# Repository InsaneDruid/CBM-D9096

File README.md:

# CBM D9096 - a PetSD+ variant
Inspired by the work of Steve J. Gray and his cbmSD-mini, the CBM D9096 is a cost- and feature-reduced version of Nils Eiler's PetSD+ board, designed specifically for headless operation in an external enclosure, connected with a true GPIB cable, similar to a D9060 or D9090.

[Schematic](https://github.com/InsaneDruid/cbm-d9096/blob/main/cbm-d9096/cbm-d9096.pdf "Schematic")  

[Bill of Materials](https://htmlpreview.github.io/?https://github.com/InsaneDruid/cbm-d9096/blob/main/cbm-d9096/bom/cbm-d9096_bom.html "Bill of Materials")

## The features
A 24-pin Centronics IEEE488/GBIP connector allows the CBM D9096 to be placed anywhere in the IEEE488 chain. This also eliminates the need for a second connector, as the IEEE488 connectors are designed to be stackable.
The SD-Card interface, the status LED and the RESET Button are implemented as pinheaders, so that the main PCB with the GBIB plug and power port can be spaced away from the parts the user needs to interact with, giving flexibility in the design of a case. Additionally, the option to use a Molex Mini Fit Jr Power Plug for connecting to an internal power supply has been implemented.

## The features that got removed
The display with its display controller, the clock, the clock battery, the buttons for interfacing with the display, and the IEC connector have been removed. The circuitry to support SD cards (mainly the 3.3 V power regulator) has also been moved to the readily available card modules. This allows the use of SD and MicroSD modules and the aforementioned flexibility in positioning these modules in a housing.

## The SD card adapters - 1.1.0 adding more options
The board now features two headers to attach readily available SD card and Micro SD card modules.
The one marked *5V SPI SD-CARD* (J3) is operating at 5 volts! The card modules attached here  MUST have appropriate level shifters installed.
Tis applies to nearly all readily available Micro SD card modules, but only some older SD card modules.
Tested and working boards are: *DEBO MICROSD 2* and *C-Control Pro Nr. 197220*
Boards that just use a voltage regulator and some passive resistors do NOT work on this header!

To use the 5V SPI SD-CARD header, JP1 needs to be set to position 2-3 (leftwards)

The one marked *3.3V SPI SD-CARD* (J5) is operating at 3.3 volts using a TXU0304 SPI level shifter and a 3.3V regulator.The card modules attached here don't need (and should *not* have!) their own level shifters.
This applies to nearly all readily available full size SD card modules. Note: this port supplies 3.3V OR 5V to the card module. Select the appropriate pin depending on the card module to connect. 

To use the 3.3V SPI SD-CARD header, JP1 needs to be set to position 1-2 (rightwards)

*Attention!* you CANNOT use two SD card modules at the same time!

## The *card detect* and *write protect* signals
Both SD card headers J3 & J5 have ground pin headers available behind the pins for the card detect ("CD") and write protect ("WP) signals (marked J4 & J6). If the attached card module doesn't provide these signals, for example all Micro SD modules, connect a 2.54mm jumper between the CD and or WP pins of J3/J5 and the associated pin of J4/J6 to permanently tie these signals to ground (permanently enable them).

## The Firmware
Andy Grady has provided a customized [firmware](https://github.com/InsaneDruid/cbm-d9096/blob/main/firmware/cbm-d9096.bin "cbm-d9096.bin") in which the button input is completely deactivated, so that the use of a voltage divider and filtered analog voltage is no longer necessary and with V1.1.0 these supporting parts are omitted. 

### Firmware installation
* Flash the [bootloader](https://github.com/InsaneDruid/cbm-d9096/blob/main/firmware/new-bootloader-for-16-MHz-petSD-plus.hex "new-bootloader-for-16-MHz-petSD-plus.hex") file to the Atmega. 
    * Set the fuse bits to Low: F7, High: D2, Extended: FC
        * low: CKSEL3=low
        * high: SPIEN=0, EESAVE=0, BOOTSZ1=0, BOOTRST=0
        * extended: BODLEVEL1=0, BODLEVEL0=0
* Install the Atmega in the board.
* Copy the [firmware](https://github.com/InsaneDruid/cbm-d9096/blob/main/firmware/cbm-d9096.bin "cbm-d9096.bin") to a FAT16 or FAT32 formatted SD-card.
* Insert the prepared card and turn on the d9096.
* On startup, the bootloader will program the firmware to the Atmega.
    * The file name is not important - the bootloader checks for a hardware tag and version number in the file.
    * During the flash operation the busy LED flickers rapidly.
    * If a valid firmware is not found, the boot loader will flash the error LED for two seconds and try to find a valid file once more.

## The LED options
The board is designed to be configured for a 2 LED or 3 LED setup:

### 2 LED variant
In the 2 LED variant power and error are combined in a *bidirectional* dual-color led (NOT common cathode or common anode!), reminiscent of how the CBM drives did. Activity is shown on a standard LED.

* install a jumper wire in place of R2
* connect a bidirectional LED between pins 3 (error) and 4 (power) of J2
* connect a standard LED between pins 1(activity) and 2 (gnd) of J2

### 3 LED variant
In the 3 LED variant power and error as well as activity are displayed with independent LED.

* don't install R4 (leave open)
* install a 330 Ohm resistor in R1, R2, R3
* connect power LED between pins 4 (power) and 2 (GND) of J2
* connect error LED between pins 3 (error) and 2 (GND) of J2
* connect activity LED between pins 1 (activity) and 2 (GND) of J2

## The printable housing option
To adapt the cheaply available Bahar enclosue 150*140*70mm project box, 3d printable parts are available.

[Printable parts on printables.com](https://www.printables.com/model/878141-cbm-d9069/ "Printable parts on printables.com")  

## The License
This work is licensed under a Creative Commons Attribution-ShareAlike 4.0 International License.  
See https://creativecommons.org/licenses/by-sa/4.0/.

## The Credits
This work would not have been possible without the work of Nils Eilers and his wonderful PetSD+. In addition, Steve J. Gray had the idea of a similar cost- and feature-reduced version of the PetSD+ when he designed his cbmSD-mini, which uses board-edge connectors and is designed to connect directly to the PETs board and case. This work inspired the CBM D9096.

Special thanks also go to Andy Grady for the customized firmware.

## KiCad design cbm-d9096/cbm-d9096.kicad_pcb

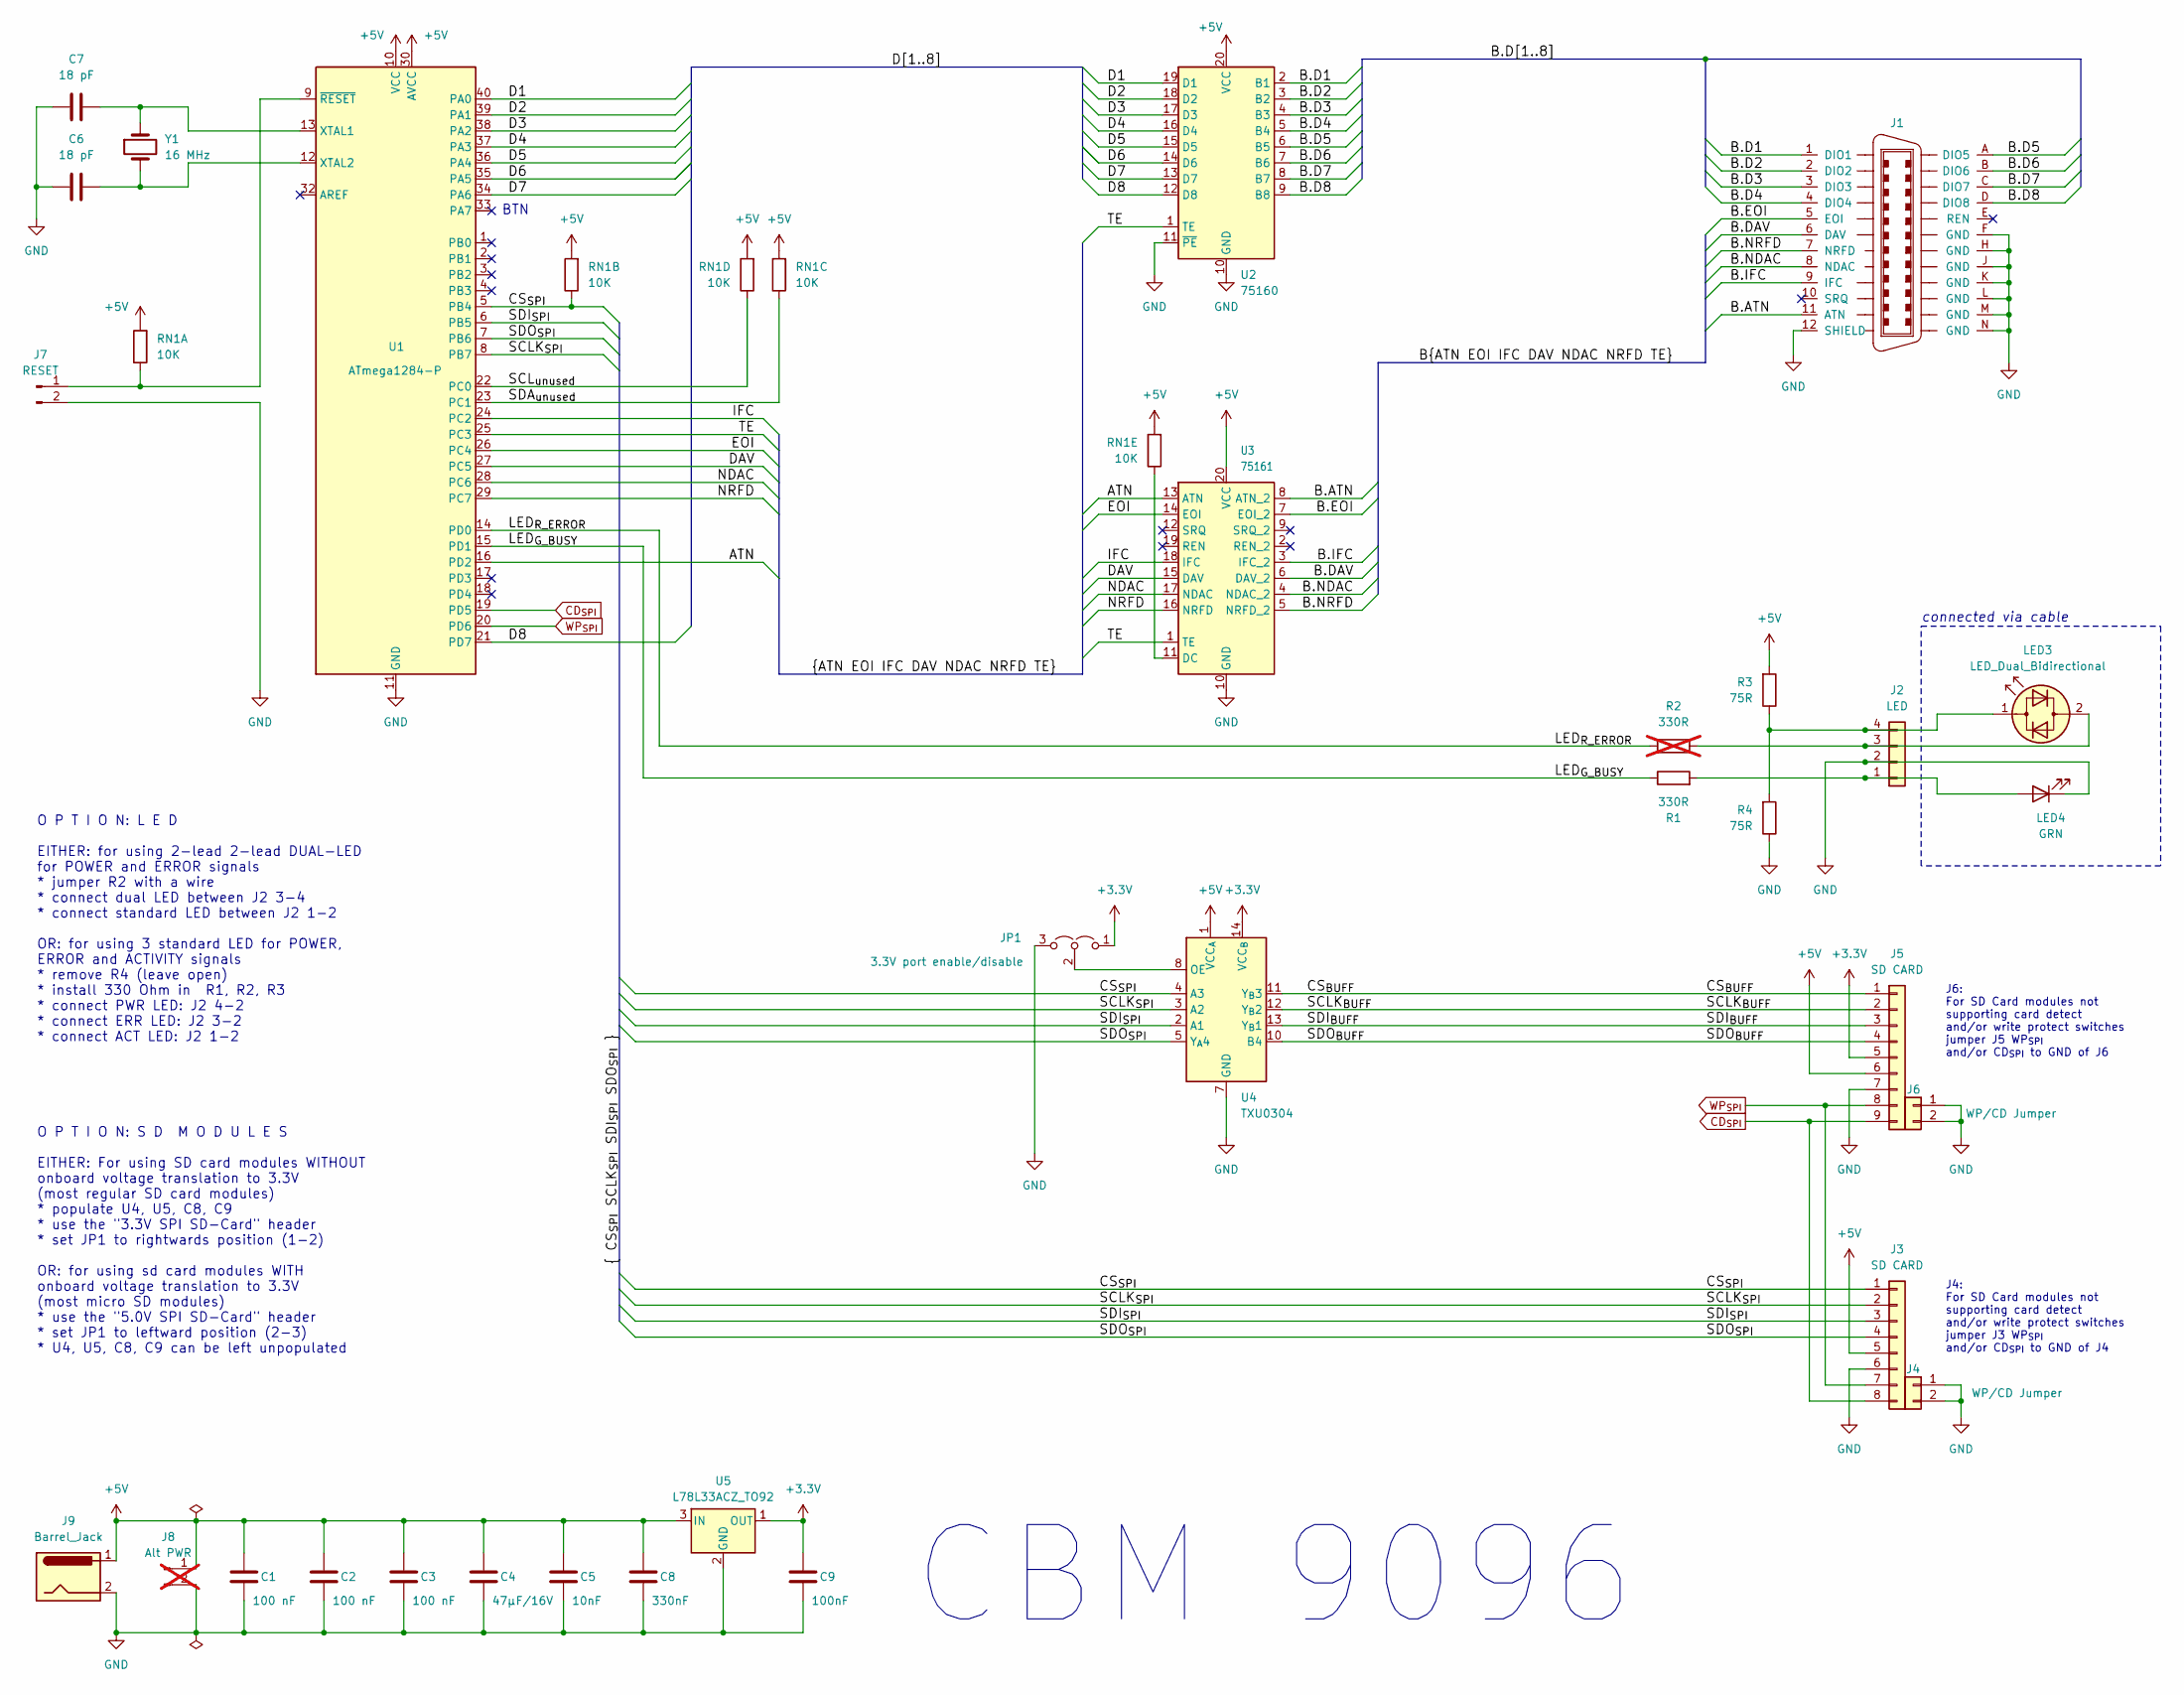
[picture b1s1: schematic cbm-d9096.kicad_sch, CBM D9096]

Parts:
C1, C2, C3: 100 nF; C_Disc_D3.8mm_W2.6mm_P2.50mm
C4: 47µF/16V; CP_Radial_D6.3mm_P2.50mm
C5: 10nF; C_Disc_D3.8mm_W2.6mm_P2.50mm
C6, C7: 18 pF; C_Disc_D3.8mm_W2.6mm_P2.50mm
C8: 330nF; C_Disc_D3.8mm_W2.6mm_P2.50mm
C9: 100nF; C_Disc_D3.8mm_W2.6mm_P2.50mm
J1: IEEE488 Header; centronix-24-female
J2: LED; PinHeader_1x04_P2.54mm_Vertical
J3: SD CARD; PinHeader_1x08_P2.54mm_Vertical
J4, J6: WP/CD Jumper; PinHeader_1x02_P2.54mm_Vertical
J5: SD CARD; PinHeader_1x09_P2.54mm_Vertical
J7: RESET; PinHeader_1x02_P2.54mm_Vertical
J8: Alt PWR; Molex_Mini-Fit_Jr_5566-02A_2x01_P4.20mm_Vertical; not fitted
J9: Barrel_Jack; BarrelJack_Horizontal
JP1: 3.3V port enable/disable; PinHeader_1x03_P2.00mm_Vertical
LED3: LED_Dual_Bidirectional
LED4: GRN; LED_D3.0mm_Clear
R1: 330R; R_Axial_DIN0207_L6.3mm_D2.5mm_P10.16mm_Horizontal
R2: 330R; R_Axial_DIN0207_L6.3mm_D2.5mm_P10.16mm_Horizontal; not fitted
R3, R4: 75R; R_Axial_DIN0207_L6.3mm_D2.5mm_P10.16mm_Horizontal
RN1: 10K; R_Array_SIP6
U1: ATmega1284-P; DIP-40_W15.24mm_Socket
U2: 75160; DIP-20_W7.62mm_Socket
U3: 75161; DIP-20_W7.62mm_Socket
U4: TXU0304; TSSOP-14_4.4x5mm_P0.65mm
U5: L78L33ACZ_TO92; TO-92L_Inline_Wide
Y1: 16 MHz; Crystal_HC49-4H_Vertical

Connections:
+3.3V: C9.1, J5.5, JP1.1 (A), U4.14 (VCC_{B}), U5.1 (OUT)
+5V: C1.2, C2.2, C3.2, C4.1, C5.1, C8.1, J3.5, J5.6, J8.1, J9.1, R3.2, RN1.1 (R1), U1.10 (VCC), U1.30 (AVCC), U2.20 (VCC), U3.20 (VCC), U4.1 (VCC_{A}), U5.3 (IN)
/ATN: U1.16 (PD2), U3.13 (ATN)
/B.ATN: J1.11 (ATN), U3.8 (ATN_2)
/B.D1: J1.1 (DIO1), U2.2 (B1)
/B.D2: J1.2 (DIO2), U2.3 (B2)
/B.D3: J1.3 (DIO3), U2.4 (B3)
/B.D4: J1.4 (DIO4), U2.5 (B4)
/B.D5: J1.A (DIO5), U2.6 (B5)
/B.D6: J1.B (DIO6), U2.7 (B6)
/B.D7: J1.C (DIO7), U2.8 (B7)
/B.D8: J1.D (DIO8), U2.9 (B8)
/B.DAV: J1.6 (DAV), U3.6 (DAV_2)
/B.EOI: J1.5 (EOI), U3.7 (EOI_2)
/B.IFC: J1.9 (IFC), U3.3 (IFC_2)
/B.NDAC: J1.8 (NDAC), U3.4 (NDAC_2)
/B.NRFD: J1.7 (NRFD), U3.5 (NRFD_2)
/CS_{BUFF}: J5.1, U4.11 (Y_{B}3)
/CS_{SPI}: J3.1, RN1.3 (R2.2), U1.5 (PB4), U4.4 (A3)
/D1: U1.40 (PA0), U2.19 (D1)
/D2: U1.39 (PA1), U2.18 (D2)
/D3: U1.38 (PA2), U2.17 (D3)
/D4: U1.37 (PA3), U2.16 (D4)
/D5: U1.36 (PA4), U2.15 (D5)
/D6: U1.35 (PA5), U2.14 (D6)
/D7: U1.34 (PA6), U2.13 (D7)
/D8: U1.21 (PD7), U2.12 (D8)
/DAV: U1.27 (PC5), U3.15 (DAV)
/EOI: U1.26 (PC4), U3.14 (EOI)
/IFC: U1.24 (PC2), U3.18 (IFC)
/LED_{G_BUSY}: R1.1, U1.15 (PD1)
/LED_{R_ERROR}: R2.1, U1.14 (PD0)
/NDAC: U1.28 (PC6), U3.17 (NDAC)
/NRFD: U1.29 (PC7), U3.16 (NRFD)
/SCLK_{BUFF}: J5.2, U4.12 (Y_{B}2)
/SCLK_{SPI}: J3.2, U1.8 (PB7), U4.3 (A2)
/SCL_{unused}: RN1.5 (R4.2), U1.22 (PC0)
/SDA_{unused}: RN1.4 (R3.2), U1.23 (PC1)
/SDI_{BUFF}: J5.3, U4.13 (Y_{B}1)
/SDI_{SPI}: J3.3, U1.6 (PB5), U4.2 (A1)
/SDO_{BUFF}: J5.4, U4.10 (B4)
/SDO_{SPI}: J3.4, U1.7 (PB6), U4.5 (Y_{A}4)
/TE: U1.25 (PC3), U2.1 (TE), U3.1 (TE)
CD_{SPI}: J3.8, J5.9, U1.19 (PD5)
GND: C1.1, C2.1, C3.1, C4.2, C5.2, C6.1, C7.1, C8.2, C9.2, J1.12 (SHIELD), J1.F (GND), J1.H (GND), J1.J (GND), J1.K (GND), J1.L (GND), J1.M (GND), J1.N (GND), J2.2, J3.6, J4.1, J4.2, J5.7, J6.1, J6.2, J7.2, J8.2, J9.2, JP1.3 (B), LED4.1 (K), R4.1, U1.11 (GND), U1.31 (GND), U2.10 (GND), U2.11 (~PE), U3.10 (GND), U4.7 (GND), U5.2 (GND); also elsewhere on the board
unnamed: J2.1, LED4.2 (A), R1.2
unnamed: J2.3, LED3.2 (AK), R2.2
unnamed: J2.4, LED3.1 (KA), R3.1, R4.2
unnamed: J7.1, RN1.2 (R1.2), U1.9 (~RESET)
unnamed: JP1.2 (C), U4.8 (OE)
unnamed: RN1.6 (R5.2), U3.11 (DC)
unnamed: C7.2, U1.13 (XTAL1), Y1.1
unnamed: C6.2, U1.12 (XTAL2), Y1.2
WP_{SPI}: J3.7, J5.8, U1.20 (PD6)

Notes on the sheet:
connected via cable
J4: For SD Card modules not supporting card detect and/or write protect switches jumper J3 WP_{SPI} and/or CD_{SPI} to GND of J4
J6: For SD Card modules not supporting card detect and/or write protect switches jumper J5 WP_{SPI} and/or CD_{SPI} to GND of J6
O P T I O N: L E D EITHER: for using 2-lead 2-lead DUAL-LED for POWER and ERROR signals * jumper R2 with a wire * connect dual LED between J2 3-4 * connect standard LED between J2 1-2 OR: for using 3 standard LED for POWER, ERROR and ACTIVITY signals * remove R4 (leave open) * install 330 Ohm in R1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
BTN
O P T I O N: S D M O D U L E S EITHER: For using SD card modules WITHOUT onboard voltage translation to 3.3V (most regular SD card modules) * populate U4, U5, C8, C9 * use the "3.3V SPI SD-Card" header * set JP1 to rightwards position (1-2) OR: for using sd card modules WITH onboard voltage transla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
CBM 9096

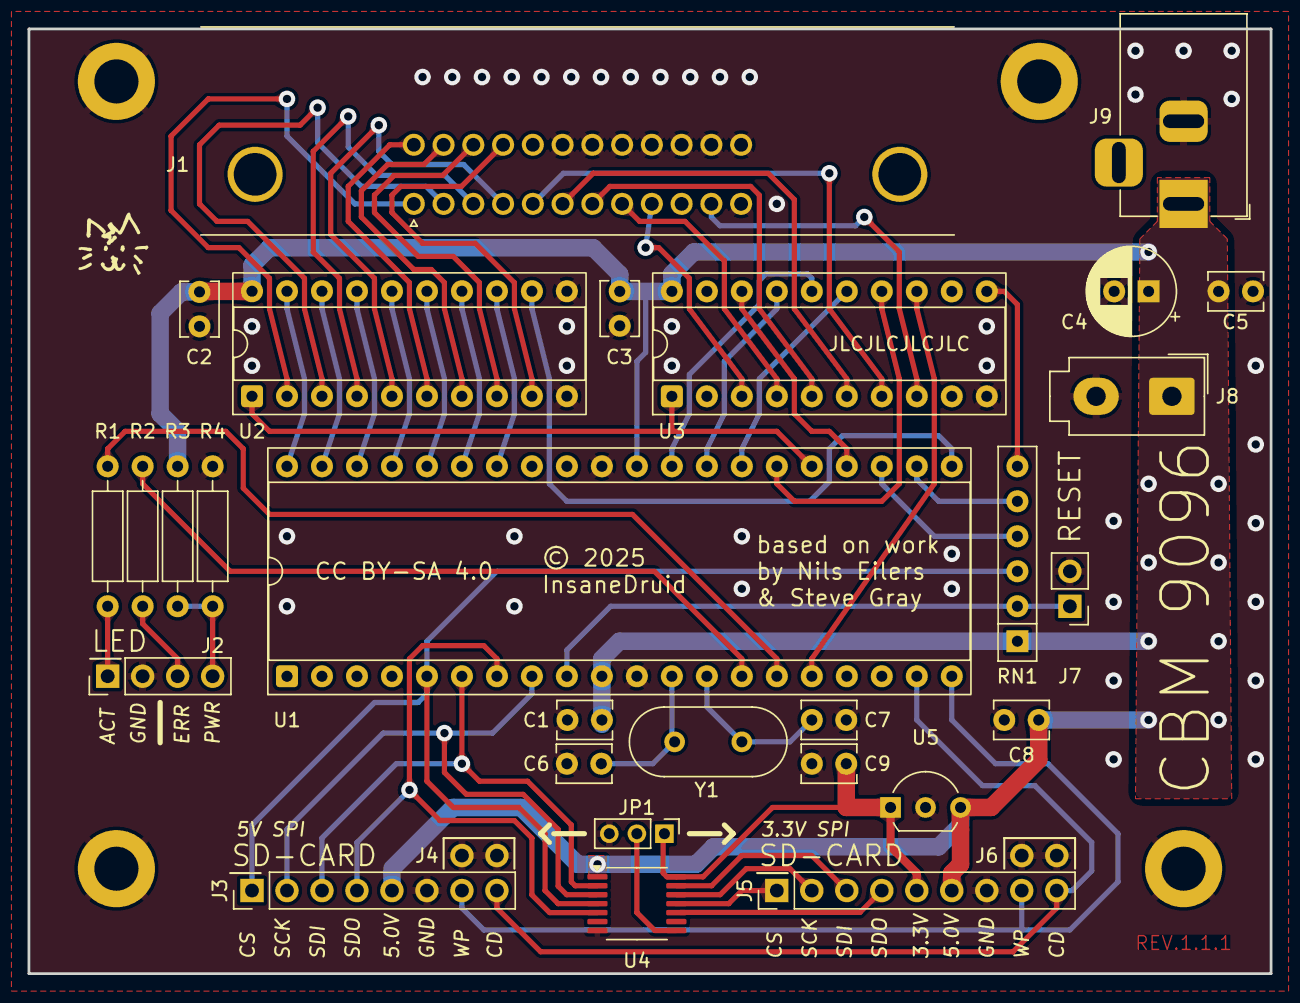
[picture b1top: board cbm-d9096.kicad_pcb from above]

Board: 2 copper layers, 90.2 x 68.6 mm, 34 parts (0 on the bottom side), 54 nets.

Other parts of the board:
MH1, MH2, MH3, MH4: MountingHole_3.2mm_M3_DIN965_Pad

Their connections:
GND: MH1.1, MH2.1, MH3.1, MH4.1; also elsewhere on the board

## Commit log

2024-07-21 - fixed schematics text referring to R4 as R2
2024-07-21 Update README.md
    - added readme section about LED variants
    - added readme section about SD card interface compatibility (required level shifters)
2024-10-30 Custom Firmware
    Added custom firmware by Andry Gray omitting the button checks in firmware, allowing for the removal of the removal of the resistor divider formed by resistors R1 and R2
2024-10-30 RN1 Description fix
    RN1 was described as 6x10K, changed to the correct 5*6K
2025-02-22 1.1.0
    - added a second SD port incorporating a 3.3V level shifter
    - removed now obsolete parts for key input
    - moved kicad project into own subfolder to allow further addons
    - fixed some..typos?!, niiice ;)
2025-03-08 fixed CD/WP silkscreen on second port
2025-03-11 added jumper to quickly enable/disable the level shifter

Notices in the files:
cbm-d9096.kicad_sch:
License: CC BY-SA 4.0
cbm-d9096/cbm-d9096.kicad_pcb:
© 2025
CC BY-SA 4.0
